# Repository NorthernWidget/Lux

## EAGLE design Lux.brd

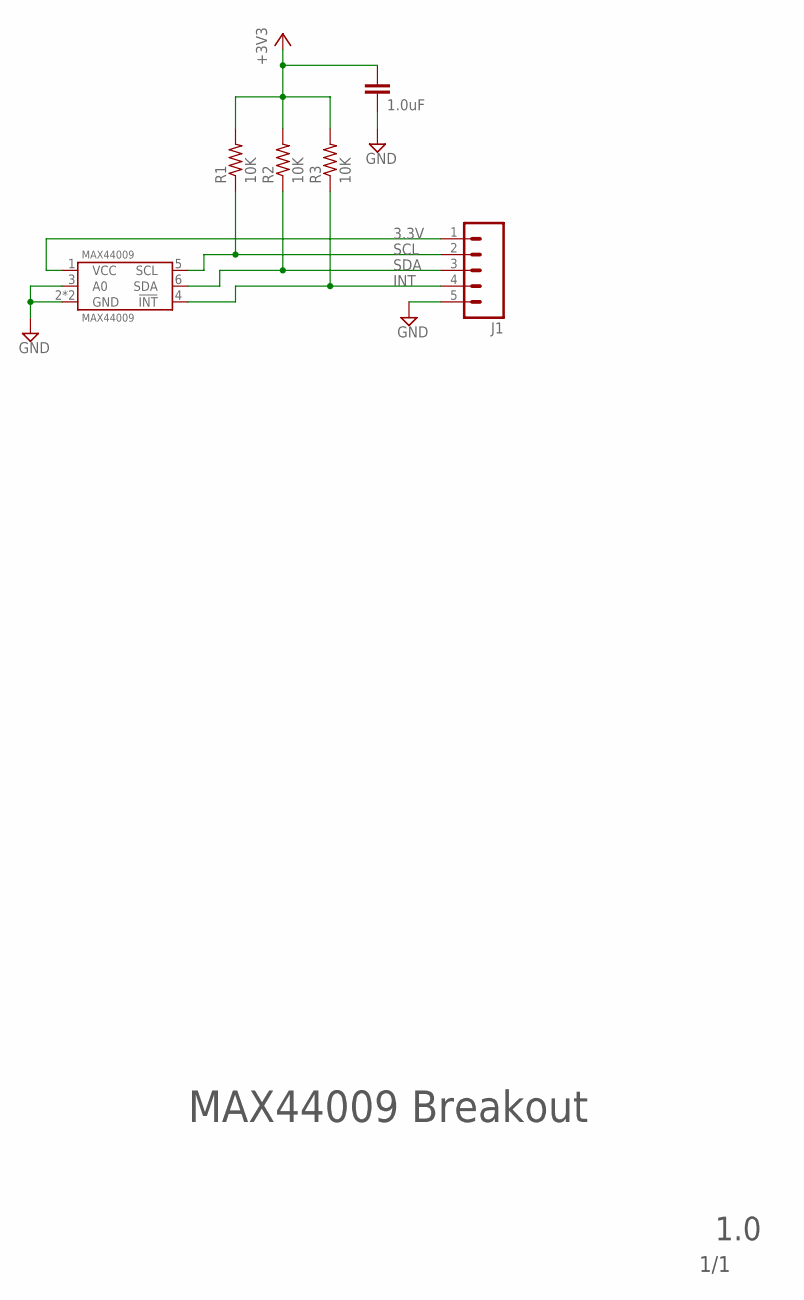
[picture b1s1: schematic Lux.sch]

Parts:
CLOCK_BATT_DECOUP: 1.0uF; C0603
J1: M05NO_SILK; 1X05_NO_SILK
MAX44009: MAX44009
R1, R2, R3: 10K; R0603

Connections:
3.3V: CLOCK_BATT_DECOUP.1, J1.1, MAX44009.1 (VCC), R1.2, R2.2, R3.2
GND: CLOCK_BATT_DECOUP.2, J1.5, MAX44009.2 (GND), MAX44009.3 (A0), MAX44009.PAD (GND)
INT: J1.4, MAX44009.4 (!INT), R3.1
SCL: J1.2, MAX44009.5 (SCL), R1.1
SDA: J1.3, MAX44009.6 (SDA), R2.1

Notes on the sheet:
MAX44009 Breakout
1.0
1/1

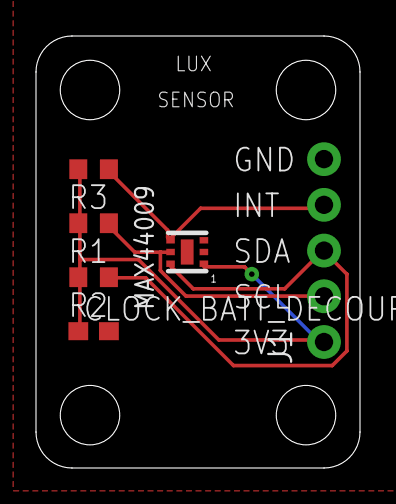
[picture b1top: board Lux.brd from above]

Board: 2 copper layers, 18.0 x 24.0 mm, 10 parts (0 on the bottom side), 5 nets.

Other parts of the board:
JP1, JP2, JP3, JP4: STAND-OFF

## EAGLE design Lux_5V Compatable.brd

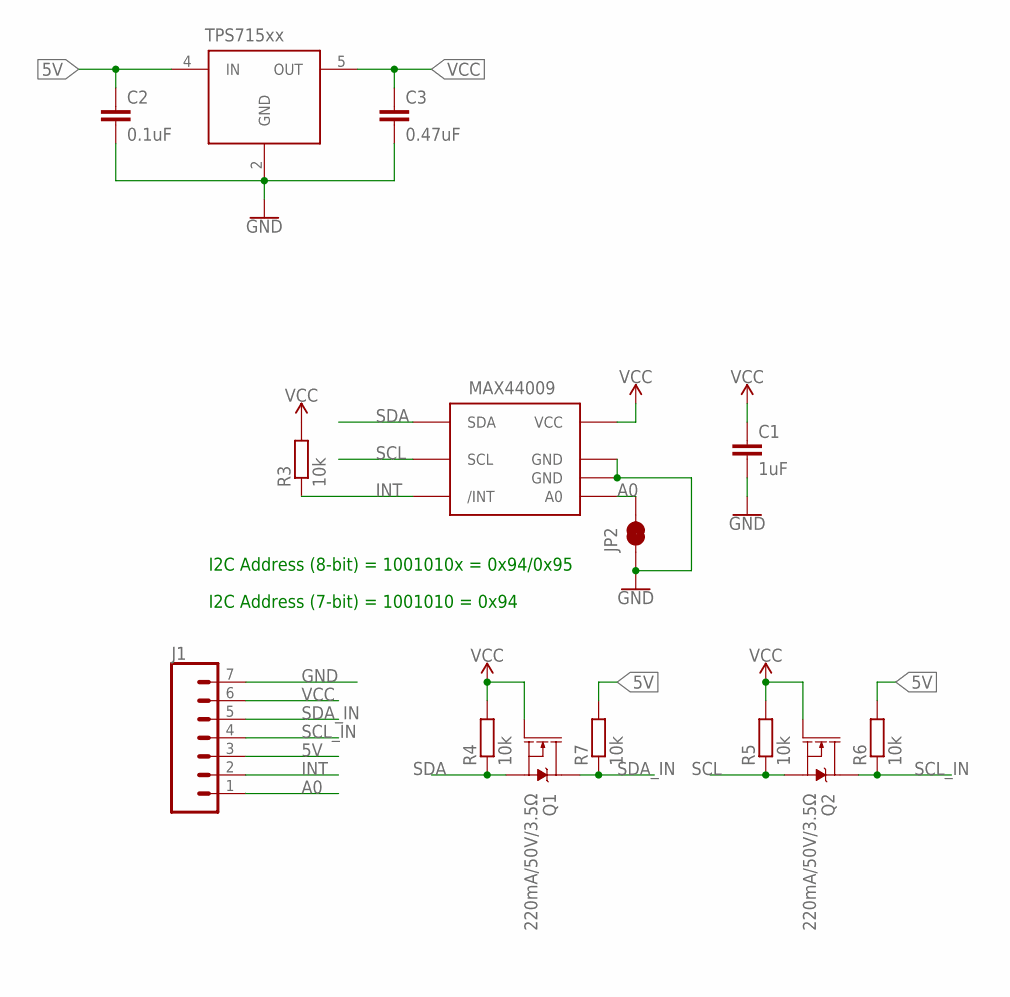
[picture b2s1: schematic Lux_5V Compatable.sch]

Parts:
C1: 1uF; C0603
C2: 0.1uF; C0603
C3: 0.47uF; C0603
J1: CONN_07; 1X07
JP2: JUMPER-SMT_2_NC_TRACE_SILK; SMT-JUMPER_2_NC_TRACE_SILK
Q1, Q2: 220mA/50V/3.5Ω; SOT23-3
R3, R4, R5, R6, R7: 10k; R0603
U$1: MAX44009; UTDFN6
U$2: TPS715XX; DCK_R-PDSO-G5

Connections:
5V: C2.1, J1.3, R6.2, R7.2, U$2.4 (IN)
A0: J1.1, JP2.2, U$1.P$3 (A0)
GND: C1.2, C2.2, C3.2, J1.7, JP2.1, U$1.P$2 (GND), U$1.P$7 (GND), U$2.2 (GND)
INT: J1.2, R3.1, U$1.P$4 (/INT)
SCL: Q2.2 (S), R5.1, U$1.P$5 (SCL)
SCL_IN: J1.4, Q2.3 (D), R6.1
SDA: Q1.2 (S), R4.1, U$1.P$6 (SDA)
SDA_IN: J1.5, Q1.3 (D), R7.1
VCC: C1.1, C3.1, J1.6, Q1.1 (G), Q2.1 (G), R3.2, R4.2, R5.2, U$1.P$1 (VCC), U$2.5 (OUT)

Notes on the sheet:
I2C Address (8-bit) = 1001010x = 0x94/0x95
I2C Address (7-bit) = 1001010 = 0x94

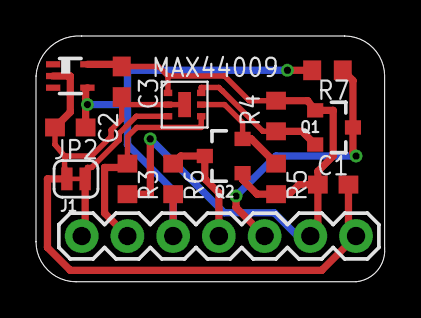
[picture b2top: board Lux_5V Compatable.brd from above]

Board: 2 copper layers, 19.4 x 13.7 mm, 14 parts (0 on the bottom side), 9 nets.

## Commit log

2017-06-28 initial design
2017-06-29 Added 5v compatable Lux breakout
    Added initial design for 5v compatable lux meter with level shifting and on board voltage regulation
2017-09-27 Add label for pin 1
2018-06-17 CC-BY-SA

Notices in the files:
parts and their libraries:
SparkFun-Connectors: Licensing: Creative Commons ShareAlike 4.0 International - https://creativecommons.org/licenses/by-sa/4.0
